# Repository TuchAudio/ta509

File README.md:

# ta509
Improved input selection board

## Purpose
Intended for the **[TuchAudio 309](../../../ta309) _Integrated Amplifier_**, together with:

- [TuchAudio 101b](../../../ta101b) Phono Pre-Amp.
- [TuchAudio 191](../../../ta191) Moving-Coil preamp (optional).
- [TuchAudio 408n](../../../ta408n) simple Volume & Balance Control.
- [TuchAudio 209](../../../ta209) Power Stage (a couple of them for _stereo_).
- [TuchAudio PSU·09](../../../psu09) Power Supply.

## Options
Besides the use of the Moving-Coil pre-amp [191](../../../ta191), which provides a **_switched_ MM/MC Phono input**,
the [408n](../../../ta408n) board might be replaced by the [TuchAudio 409n](../../../ta409n), which adds **Tone controls** (Baxandall-type).

## Inputs
- **Phono with RIAA equalisation:** both DIN and RCA connectors, 3.6 mV/110 kOhm (optional: _Moving Coil_ input via the [191](../../../ta191) board)
- **Line input:** both DIN and RCA connectors, 180 mV/900 kOhm (suitable for _ceramic_ cartridges)
- **Tape Playback:** thru RCA (180 mV/47 k) and DIN (0.48 V/16.5 k) connectors.

## Outputs
- Line out: 180 mV (intended for a suitable poweramp, like [TuchAudio 209](../../../ta209) thru a [408](../../../ta408n)/[409](../../../ta409n) _volume_ board).
- Tape Rec (RCA): 180 mV
- Tape Rec (DIN): 5.3 mV over 10 kohm

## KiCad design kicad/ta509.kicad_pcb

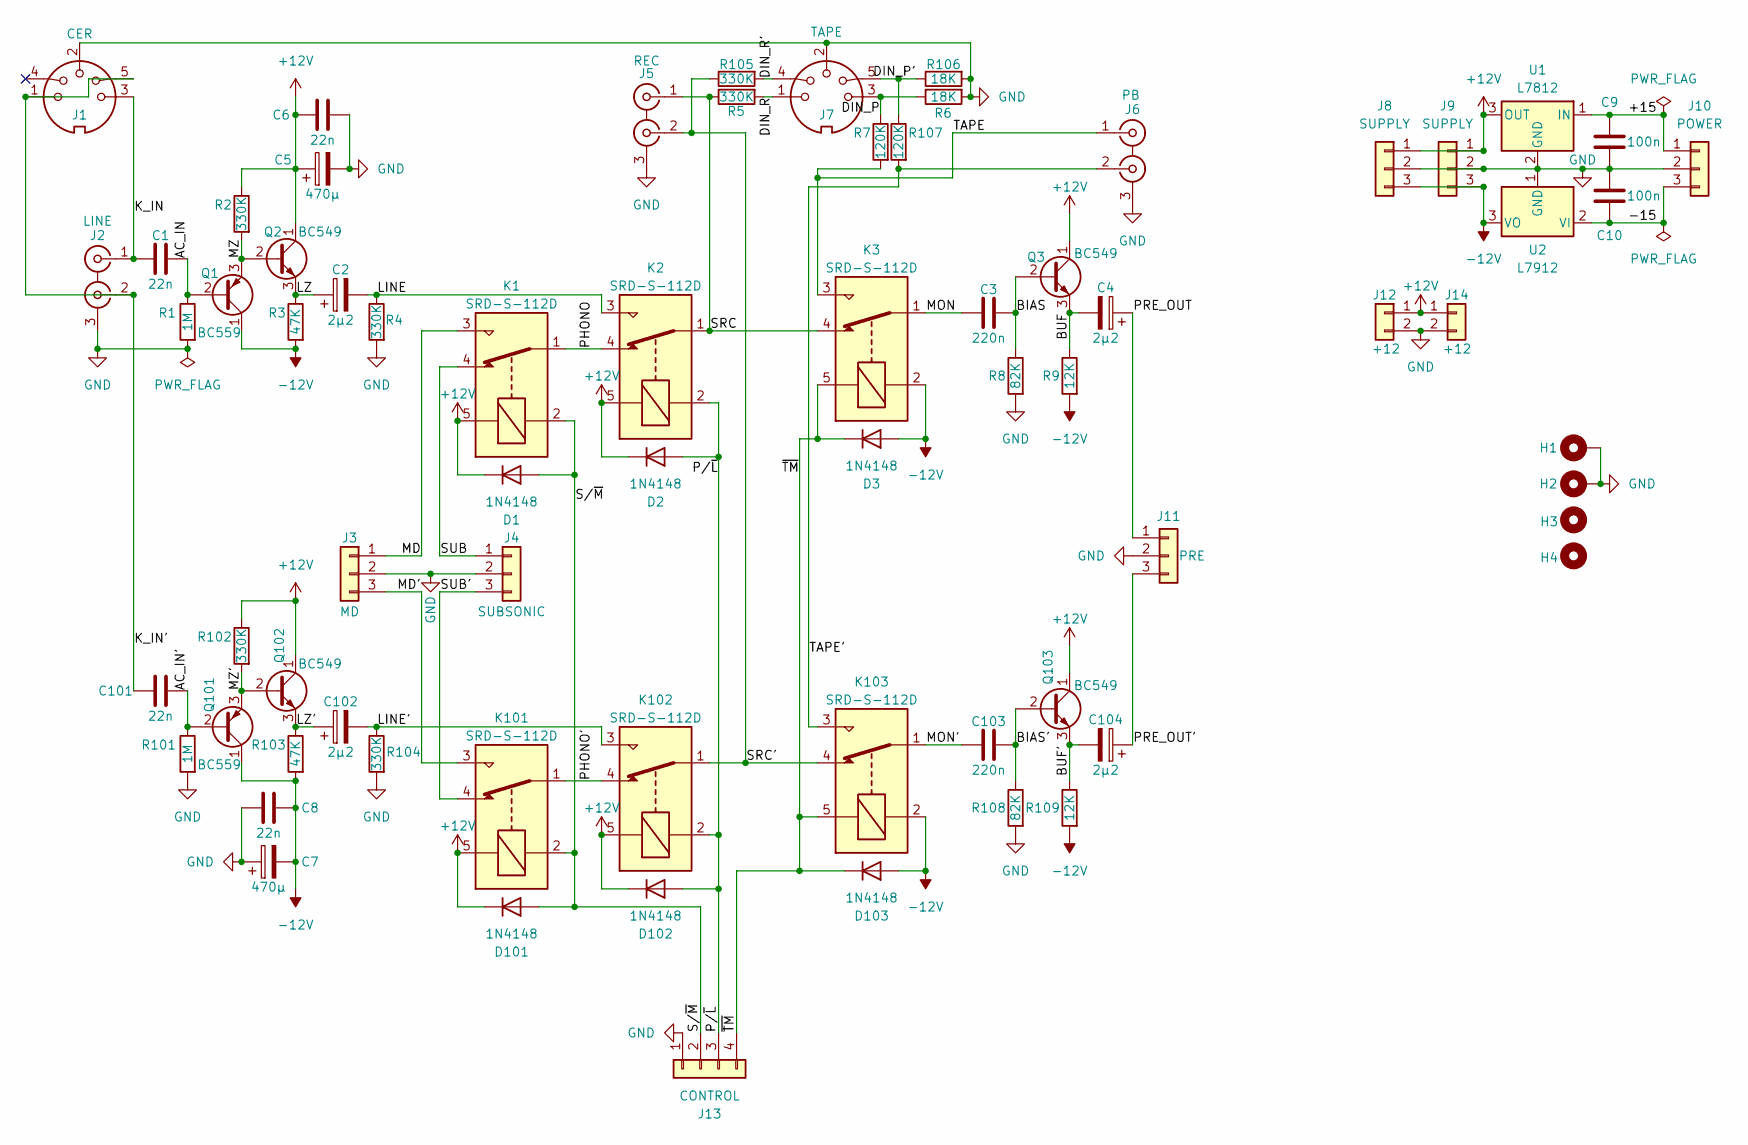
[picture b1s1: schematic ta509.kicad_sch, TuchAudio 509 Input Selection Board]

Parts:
C1, C101: 22n; C_Rect_L7.2mm_W2.5mm_P5.00mm_FKS2_FKP2_MKS2_MKP2
C2, C4, C102, C104: 2µ2; CP_Radial_D4.0mm_P1.50mm
C3, C103: 220n; C_Rect_L7.2mm_W3.5mm_P5.00mm_FKS2_FKP2_MKS2_MKP2
C5, C7: 470µ; CP_Radial_D10.0mm_P5.00mm
C6, C8: 22n; C_Disc_D6.0mm_W2.5mm_P5.00mm
C9, C10: 100n; C_Rect_L7.2mm_W2.5mm_P5.00mm_FKS2_FKP2_MKS2_MKP2
D1, D2, D3, D101, D102, D103: 1N4148; D_DO-35_SOD27_P7.62mm_Horizontal
H1, H2: MountingHole_Pad; MountingHole_3.2mm_M3_DIN965_Pad
H3, H4: MountingHole; MountingHole_3.2mm_M3_DIN965
J1: CER; DIN 5-180deg
J2: LINE; 2xRCA_vertical
J3: MD; PinHeader_1x03_P2.54mm_Vertical
J4: SUBSONIC; PinHeader_1x03_P2.54mm_Vertical
J5: REC; 2xRCA_vertical
J6: PB; 2xRCA_vertical
J7: TAPE; DIN 5-180deg
J8, J9: SUPPLY; PinHeader_1x03_P2.54mm_Vertical
J10: POWER; PinHeader_1x03_P2.54mm_Vertical
J11: PRE; PinHeader_1x03_P2.54mm_Vertical
J12, J14: +12; PinHeader_1x02_P2.54mm_Vertical
J13: CONTROL; PinHeader_1x04_P2.54mm_Vertical
K1, K2, K3, K101, K102, K103: SRD-S-112D; Relay_SPDT_SANYOU_SRD_Series_Form_C
Q1, Q101: BC559; TO-92_Inline
Q2, Q3, Q102, Q103: BC549; TO-92_Inline
R1, R101: 1M; R_Axial_DIN0207_L6.3mm_D2.5mm_P10.16mm_Horizontal
R2, R4, R5, R102, R104, R105: 330K; R_Axial_DIN0207_L6.3mm_D2.5mm_P10.16mm_Horizontal
R3, R103: 47K; R_Axial_DIN0207_L6.3mm_D2.5mm_P10.16mm_Horizontal
R6, R106: 18K; R_Axial_DIN0207_L6.3mm_D2.5mm_P10.16mm_Horizontal
R7, R107: 120K; R_Axial_DIN0207_L6.3mm_D2.5mm_P10.16mm_Horizontal
R8, R108: 82K; R_Axial_DIN0207_L6.3mm_D2.5mm_P10.16mm_Horizontal
R9, R109: 12K; R_Axial_DIN0207_L6.3mm_D2.5mm_P10.16mm_Horizontal
U1: L7812; TO-220-3_Vertical
U2: L7912; TO-220-3_Vertical

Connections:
+12V: C5.1, C6.1, D1.1 (K), D2.1 (K), D101.1 (K), D102.1 (K), J8.1, J9.1, J12.1, J14.1, K1.5, K2.5, K101.5, K102.5, Q2.1 (C), Q3.1 (C), Q102.1 (C), Q103.1 (C), R2.1, R102.1, U1.3 (OUT)
-12V: C7.2, C8.1, D3.2 (A), D103.2 (A), J8.3, J9.3, K3.2, K103.2, Q1.1 (C), Q101.1 (C), R3.2, R9.2, R103.2, R109.2, U2.3 (VO)
/+15: C9.2, J10.1, U1.1 (IN)
/-15: C10.1, J10.3, U2.2 (VI)
/AC_IN: C1.2, Q1.2 (B), R1.1
/AC_IN': C101.2, Q101.2 (B), R101.1
/BIAS: C3.2, Q3.2 (B), R8.1
/BIAS': C103.2, Q103.2 (B), R108.1
/BUF: C4.2, Q3.3 (E), R9.1
/BUF': C104.2, Q103.3 (E), R109.1
/DIN_P: J7.3, R6.1, R7.1
/DIN_P': J7.5, R106.1, R107.1
/DIN_R: J7.1, R5.2
/DIN_R': J7.4, R105.2
/K_IN: C1.1, J1.3, J2.1 (IN1)
/K_IN': C101.1, J1.1, J1.5, J2.2 (IN2)
/LINE: C2.2, K2.3, R4.1
/LINE': C102.2, K102.3, R104.1
/LZ: C2.1, Q2.3 (E), R3.1
/LZ': C102.1, Q102.3 (E), R103.1
/MD: J3.1, K1.3
/MD': J3.3, K101.3
/MON: C3.1, K3.1
/MON': C103.1, K103.1
/MZ: Q1.3 (E), Q2.2 (B), R2.2
/MZ': Q101.3 (E), Q102.2 (B), R102.2
/PHONO: K1.1, K2.4
/PHONO': K101.1, K102.4
/PRE_OUT: C4.1, J11.1
/PRE_OUT': C104.1, J11.3
/P/~L: D2.2 (A), D102.2 (A), J13.3, K2.2, K102.2
/SRC: J5.1 (IN1), K2.1, K3.4, R5.1
/SRC': J5.2 (IN2), K102.1, K103.4, R105.1
/SUB: J4.1, K1.4
/SUB': J4.3, K101.4
/S/~M: D1.2 (A), D101.2 (A), J13.2, K1.2, K101.2
/TAPE: J6.1 (IN1), K3.3, R7.2
/TAPE': J6.2 (IN2), K103.3, R107.2
/~TM: D3.1 (K), D103.1 (K), J13.4, K3.5, K103.5
GND: C5.2, C6.2, C7.1, C8.2, C9.1, C10.2, H1.1, H2.1, J1.2, J2.3 (EXT), J3.2, J4.2, J5.3 (EXT), J6.3 (EXT), J7.2, J8.2, J9.2, J10.2, J11.2, J12.2, J13.1, J14.2, R1.2, R4.2, R6.2, R8.2, R101.2, R104.2, R106.2, R108.2, U1.2 (GND), U2.1 (GND)

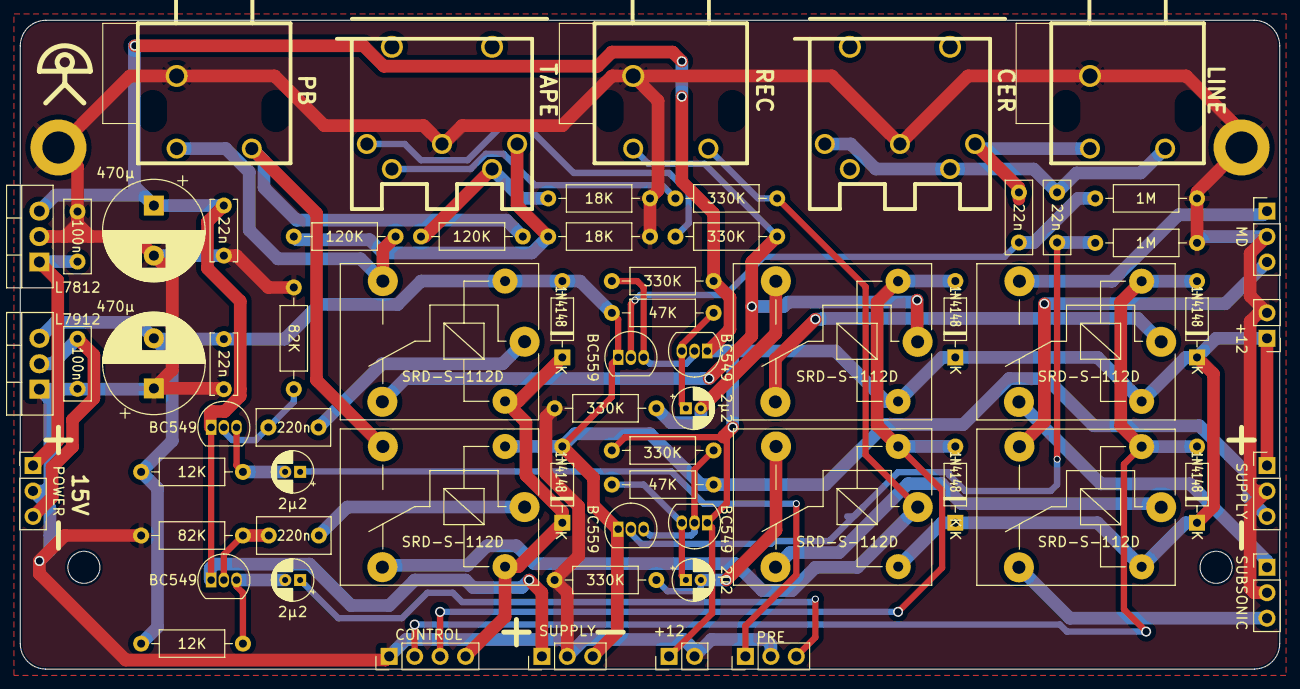
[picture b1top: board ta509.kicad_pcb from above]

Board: 2 copper layers, 125.7 x 64.8 mm, 70 parts (0 on the bottom side), 40 nets.

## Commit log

2025-11-08 add KiCAD files
2025-11-10 describe suggested boards and inputs
    Added purpose, options, and inputs sections to README.
2025-11-24 fix inputs and outputs
2025-11-24 add lots of links
